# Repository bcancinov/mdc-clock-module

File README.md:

# mdc-clock-module
Modular Detector Controller Clock Module

## Overview
Clock generator module with jitter cleaning. Takes a 10 MHz input and generates an ultra low jitter 100 MHz output with zero delay for the detector sequencer.
Provides up to three low-jitter synchronized clock outputs.

## Key ICs
- Jitter attenuator / clock multiplier: `SI5394J-A-GM`
  - DSPLL + MultiSynth architecture for ultra-low jitter clock generation.
  - Supports free-run, synchronous, and holdover modes with hitless switching between inputs.
  - Programmable via serial interface with on-chip NVM for power-up configuration.
  - A-grade devices use an external XTAL or XO reference.
- LDO: `TPS7A20`
  - Low-noise, high-PSRR LDO for clean supply rails to the timing IC.
  - Low IQ with good load/line transient performance for sensitive analog circuits.

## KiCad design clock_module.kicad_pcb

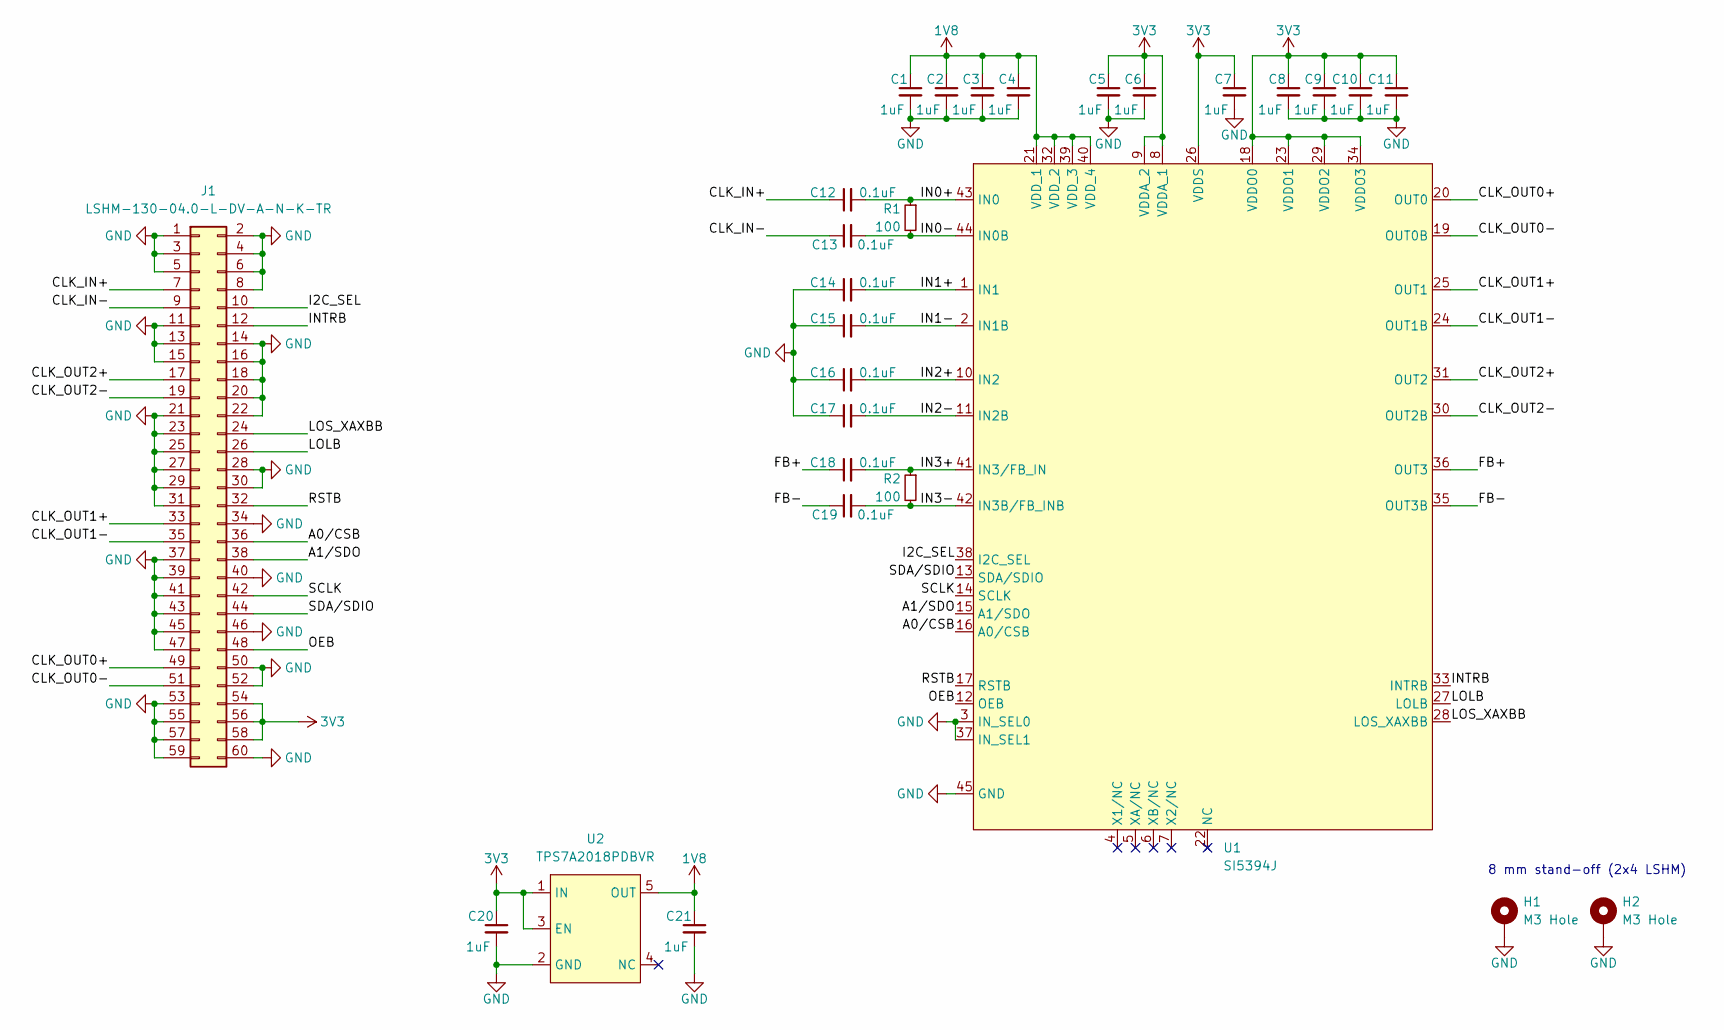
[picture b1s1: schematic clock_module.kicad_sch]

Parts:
C1, C2, C3, C4, C5, C6, C7, C8, C9, C10, C11, C20, C21: 1uF; C_0402_1005Metric; MPN C0402X7R100-105KNP-CT
C12, C13, C14, C15, C16, C17, C18, C19: 0.1uF; C_0402_1005Metric; MPN GCM155R71C104KA55J
H1, H2: M3 Hole; MountingHole_3.2mm_M3_Pad_Via
J1: LSHM-130-04.0-L-DV-A-N-K-TR; SAMTEC_LSHM-130-04.0-L-DV-A-N-K-TR; MPN LSHM-130-04.0-L-DV-A-N-K-TR
R1, R2: 100; R_0402_1005Metric; MPN CRCW0402100RFKEDHP
U1: SI5394J; QFN50P700X700X90-45N; MPN SI5394J-A-GM
U2: TPS7A2018PDBVR; SOT-23-5; MPN TPS7A2018PDBVR

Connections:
1V8: C1.1, C2.1, C3.1, C4.1, C21.1, U1.21 (VDD_1), U1.32 (VDD_2), U1.39 (VDD_3), U1.40 (VDD_4), U2.5 (OUT)
3V3: C5.1, C6.1, C7.1, C8.1, C9.1, C10.1, C11.1, C20.1, J1.54, J1.56, J1.58, U1.8 (VDDA_1), U1.9 (VDDA_2), U1.18 (VDDO0), U1.23 (VDDO1), U1.26 (VDDS), U1.29 (VDDO2), U1.34 (VDDO3), U2.1 (IN), U2.3 (EN)
/A0/CSB: J1.36, U1.16 (A0/CSB)
/A1/SDO: J1.38, U1.15 (A1/SDO)
/CLK_IN+: C12.1, J1.7
/CLK_IN-: C13.1, J1.9
/CLK_OUT0+: J1.49, U1.20 (OUT0)
/CLK_OUT0-: J1.51, U1.19 (OUT0B)
/CLK_OUT1+: J1.33, U1.25 (OUT1)
/CLK_OUT1-: J1.35, U1.24 (OUT1B)
/CLK_OUT2+: J1.17, U1.31 (OUT2)
/CLK_OUT2-: J1.19, U1.30 (OUT2B)
/FB+: C18.1, U1.36 (OUT3)
/FB-: C19.1, U1.35 (OUT3B)
/I2C_SEL: J1.10, U1.38 (I2C_SEL)
/IN0+: C12.2, R1.1, U1.43 (IN0)
/IN0-: C13.2, R1.2, U1.44 (IN0B)
/IN1+: C14.2, U1.1 (IN1)
/IN1-: C15.2, U1.2 (IN1B)
/IN2+: C16.2, U1.10 (IN2)
/IN2-: C17.2, U1.11 (IN2B)
/IN3+: C18.2, R2.1, U1.41 (IN3/FB_IN)
/IN3-: C19.2, R2.2, U1.42 (IN3B/FB_INB)
/INTRB: J1.12, U1.33 (INTRB)
/LOLB: J1.26, U1.27 (LOLB)
/LOS_XAXBB: J1.24, U1.28 (LOS_XAXBB)
/OEB: J1.48, U1.12 (OEB)
/RSTB: J1.32, U1.17 (RSTB)
/SCLK: J1.42, U1.14 (SCLK)
/SDA/SDIO: J1.44, U1.13 (SDA/SDIO)
GND: C1.2, C2.2, C3.2, C4.2, C5.2, C6.2, C7.2, C8.2, C9.2, C10.2, C11.2, C14.1, C15.1, C16.1, C17.1, C20.2, C21.2, H1.1, H2.1, J1.1, J1.2, J1.3, J1.4, J1.5, J1.6, J1.8, J1.11, J1.13, J1.14, J1.15, J1.16, J1.18, J1.20, J1.21, J1.22, J1.23, J1.25, J1.27, J1.28, J1.29, J1.30, J1.31, J1.34, J1.37, J1.39, J1.40, J1.41, J1.43, J1.45, J1.46, J1.47, J1.50, J1.52, J1.53, J1.55, J1.57, J1.59, J1.60, U1.3 (IN_SEL0), U1.37 (IN_SEL1), U1.45 (GND), U2.2 (GND)

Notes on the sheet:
8 mm stand-off (2x4 LSHM)

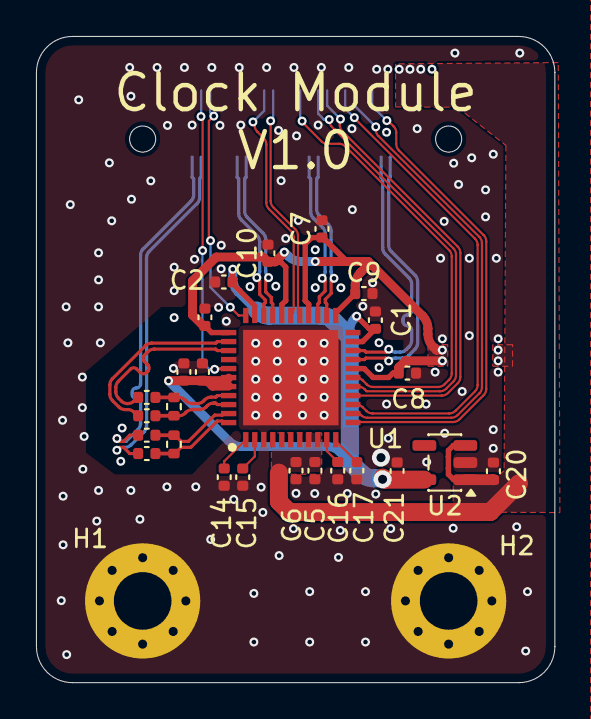
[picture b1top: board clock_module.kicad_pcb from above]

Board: 4 copper layers, 28.8 x 35.9 mm, 28 parts (1 on the bottom side), 31 nets.

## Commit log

2026-02-06 Add BOM
2026-02-06 update readme and docs
